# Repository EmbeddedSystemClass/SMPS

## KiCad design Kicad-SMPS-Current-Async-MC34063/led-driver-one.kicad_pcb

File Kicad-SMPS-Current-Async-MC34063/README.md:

SMPS LED Driver
---------------

This project provides a small LED driver circuit using a common switch mode
IC MC34063 in a constant current configuration. The circuit is designed to
deliver up to 1.5A, the maximum current of the MC34063. An opamp is provided to
amplify the current sense voltage to the required 1.25V of the MC34063.

An extra resistor is provided to allow adaptation of the circuit as a buck
converter. This must be omitted for the constant current application. Two
resistors must be shorted and the opamp omitted for the buck converter
application. See notes on the schematic diagram.

More information is provided at [Jiggerjuice](http://www.jiggerjuice.info/electronics/projects/power/LED-drivers.html).

(c) K. Sarkies 07/02/2018

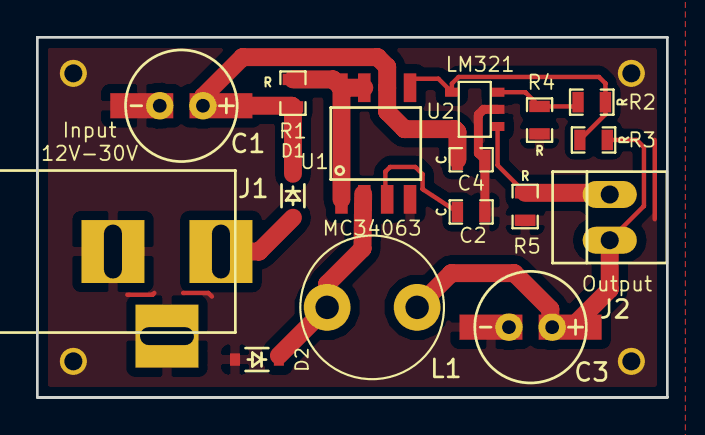
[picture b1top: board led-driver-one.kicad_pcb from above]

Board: 2 copper layers, 35.0 x 20.0 mm, 20 parts (0 on the bottom side), 10 nets.

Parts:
C1, C3: CP; RADIAL_TABBED_2.5mm_6.3mm
C2, C4: C; SM0603_Capa
D1, D2: CUS15S30; SOD-323
J1: Input 12V-30V; BARREL_JACK
J2: Output; PINHEAD1-2
J3, J3#2, J3#3, J3#4: Conn_01x01; THROUGHVIA
L1: L; L_Radial_D7.8mm_P5.00mm_Fastron_07HCP
R1, R2, R3, R4, R5: R; SM0603_Resistor
U1: MC34063; SOIC_08_4.0mm_5.0mm_1.27mm
U2: LM321; SOT23-5

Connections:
/Vcc: C1.1, C4.1, D1.1, R1.2, U1.6, U2.5
Earth: C1.2, C2.2, C3.2, C4.2, D2.2, J1.2, J1.3, J3.1, J3#2.1, J3#3.1, J3#4.1, R4.1, R5.2, U1.4, U2.2
unnamed: C2.1, U1.3
unnamed: C3.1, J2.1, L1.2, R3.1
unnamed: D1.2, J1.1
unnamed: D2.1, L1.1, U1.2
unnamed: J2.2, R5.1, U2.1
unnamed: R1.1, U1.1, U1.7, U1.8
unnamed: R2.1, R3.2, U1.5, U2.4
unnamed: R2.2, R4.2, U2.3

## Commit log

2017-11-20 Modification of gEDA circuits and removal of PCB for LED driver. Add LED-Driver as a Kicad board including PCB.
2017-11-20 Name change for ARM firmware.
2018-01-18 Rebuild PCB to correct errors and generate group of eight circuits.
2018-01-20 Update PCB to make all sub-boards identical. Remove overhang on silk screen part of Barrel-Jack footprint.
2018-02-06 Fix problem with current limiting resistor and also silk screen of diodes.
